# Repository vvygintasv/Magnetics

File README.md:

# Magnetics
Repository for reading Mag3100 sensord with stm controllers

Hello!
Your task is to read MAG3100 magnetic field and acceleration readings using stm32 controllers.( prefably stm32 nucleo series)

Rules:
Your code must be easy to read, well commented and easily integratable.

Code usafe must have examples.
Program must have user guide.

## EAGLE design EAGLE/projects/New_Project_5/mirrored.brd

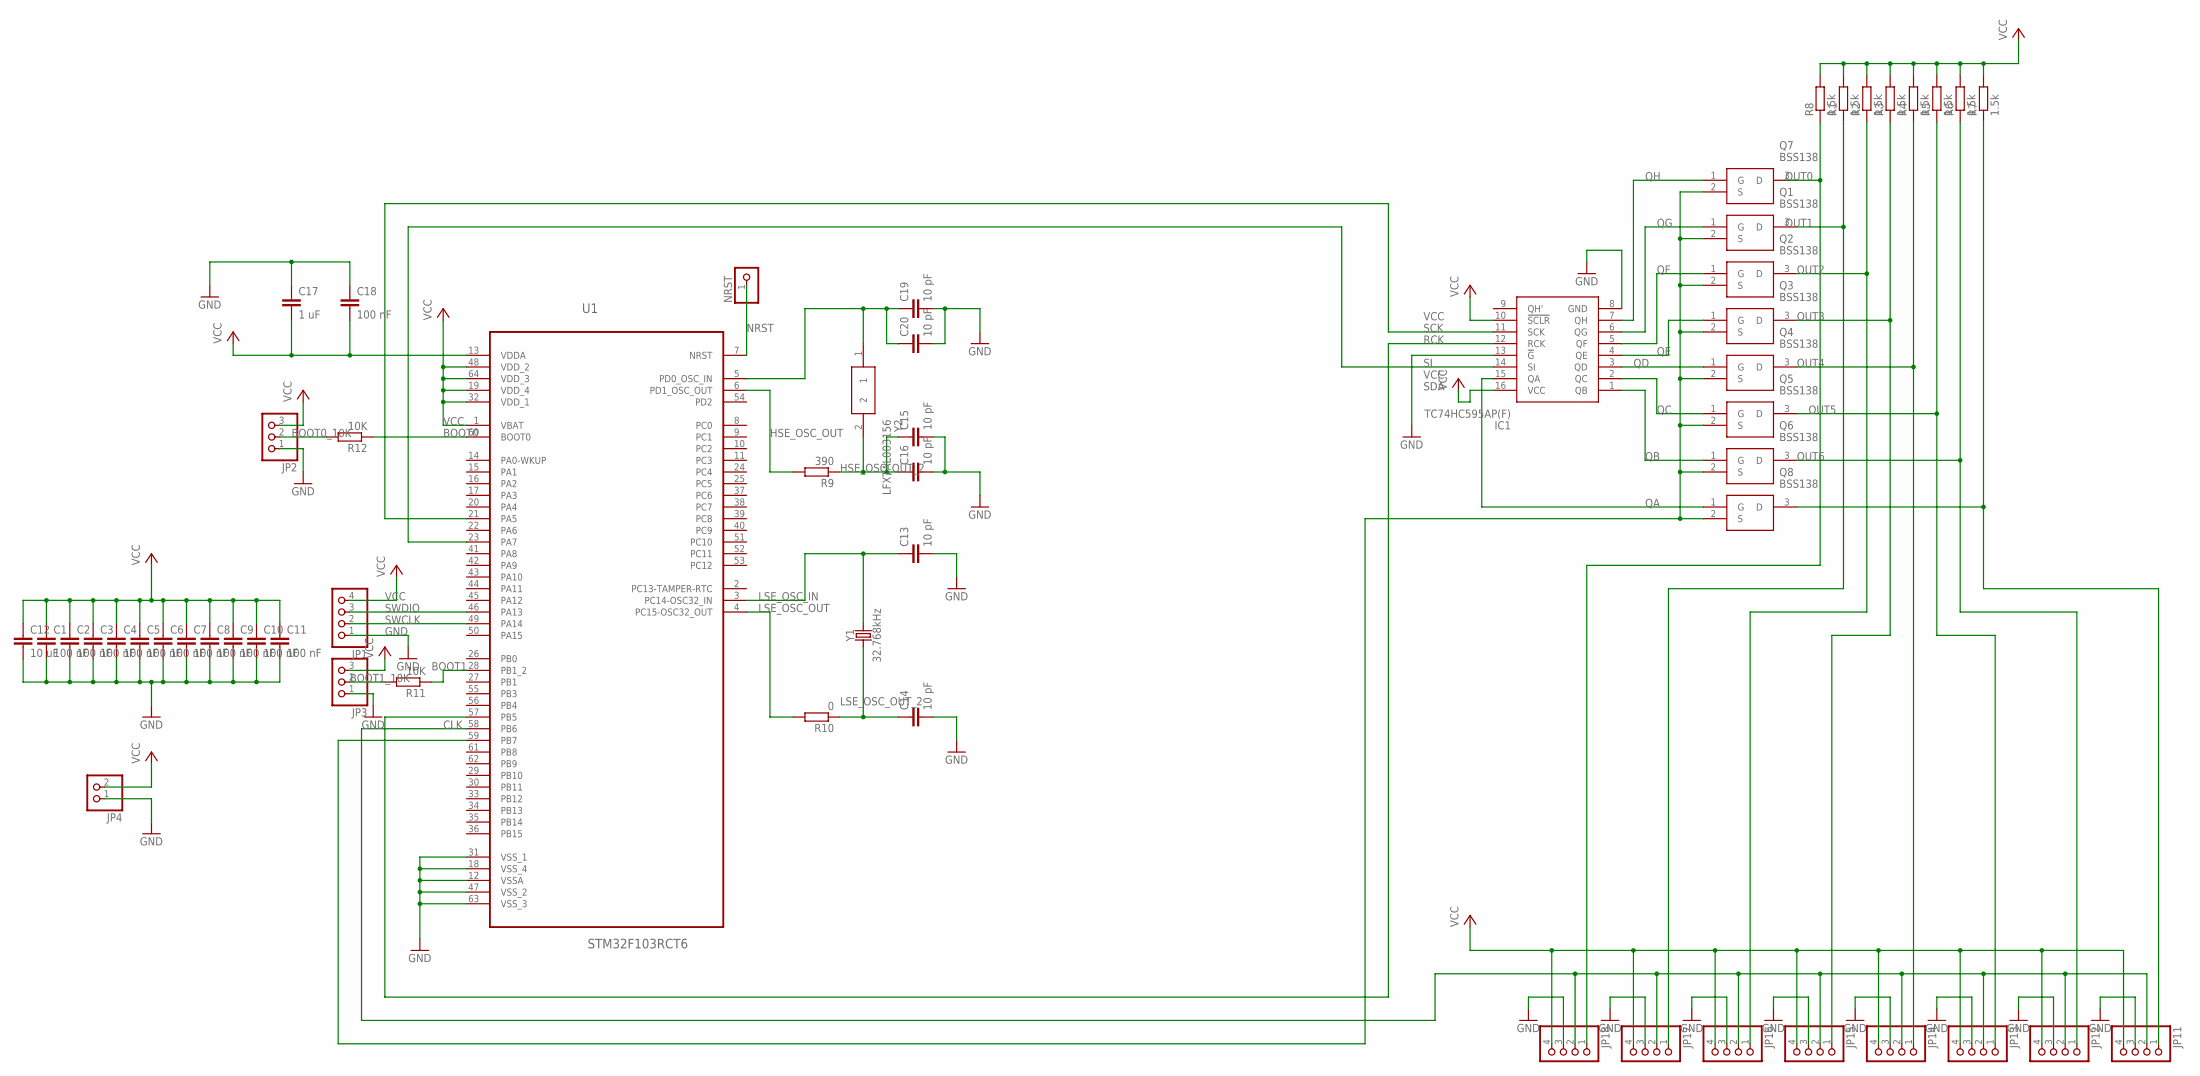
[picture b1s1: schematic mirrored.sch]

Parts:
C1, C2, C3, C4, C5, C6, C7, C8, C9, C10, C11, C18: 100 nF; C0603
C12: 10 uF; C0603
C13, C14, C15, C16, C19, C20: 10 pF; C0805
C17: 1 uF; C0603
IC1: TC74HC595AP(F); DIP762W60P254L1925H445Q16N
JP1, JP11, JP12, JP13, JP14, JP15, JP16, JP17, JP18: PINHD-1X4; 1X04
JP2, JP3: PINHD-1X3; 1X03
JP4: PINHD-1X2; 1X02
NRST: PINHD-1X1; 1X01
Q1, Q2, Q3, Q4, Q5, Q6, Q7, Q8: BSS138; SOT95P240X120-3N
R1, R2, R3, R4, R5, R6, R7, R8: 1.5k; 0207/15
R9: 390; 0207/15
R10: 0; 0207/15
R11, R12: 10K; 0207/15
U1: STM32F103RCT6; QFP50P1200X1200X160-64N
Y1: 32.768kHz; CRYSTAL-PTH-2X6-CYL
Y2: LFXTAL003156; IQD-HC-49-4H

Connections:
BOOT0: R12.1, U1.60 (BOOT0)
BOOT0_10K: JP2.2, R12.2
BOOT1: R11.1, U1.28 (PB1_2)
BOOT1_10K: JP3.2, R11.2
CLK: JP11.2, JP12.2, JP13.2, JP14.2, JP15.2, JP16.2, JP17.2, JP18.2, U1.58 (PB6)
GND: C1.2, C2.2, C3.2, C4.2, C5.2, C6.2, C7.2, C8.2, C9.2, C10.2, C11.2, C12.2, C13.2, C14.2, C15.2, C16.2, C17.1, C18.1, C19.2, C20.2, IC1.8 (GND), IC1.13 (!G), JP1.1, JP2.1, JP3.1, JP4.1, JP11.3, JP12.3, JP13.3, JP14.3, JP15.3, JP16.3, JP17.3, JP18.3, U1.12 (VSSA), U1.18 (VSS_4), U1.31 (VSS_1), U1.47 (VSS_2), U1.63 (VSS_3)
HSE_OSC_IN: C19.1, C20.1, U1.5 (PD0_OSC_IN), Y2.1
HSE_OSC_OUT: R9.2, U1.6 (PD1_OSC_OUT)
HSE_OSC_OUT_2: C15.1, C16.1, R9.1, Y2.2
LSE_OSC_IN: C13.1, U1.3 (PC14-OSC32_IN), Y1.2
LSE_OSC_OUT: R10.2, U1.4 (PC15-OSC32_OUT)
LSE_OSC_OUT_2: C14.1, R10.1, Y1.1
NRST: NRST.1, U1.7 (NRST)
OUT0: JP18.1, Q7.3 (D), R8.1
OUT1: JP17.1, Q1.3 (D), R1.1
OUT2: JP16.1, Q2.3 (D), R2.1
OUT3: JP15.1, Q3.3 (D), R3.1
OUT4: JP14.1, Q4.3 (D), R4.1
OUT5: JP13.1, Q5.3 (D), R5.1
OUT6: JP12.1, Q6.3 (D), R6.1
OUT7: JP11.1, Q8.3 (D), R7.1
QA: IC1.15 (QA), Q8.1 (G)
QB: IC1.1 (QB), Q6.1 (G)
QC: IC1.2 (QC), Q5.1 (G)
QD: IC1.3 (QD), Q4.1 (G)
QE: IC1.4 (QE), Q3.1 (G)
QF: IC1.5 (QF), Q2.1 (G)
QG: IC1.6 (QG), Q1.1 (G)
QH: IC1.7 (QH), Q7.1 (G)
RCK: IC1.12 (RCK), U1.57 (PB5)
SCK: IC1.11 (SCK), U1.21 (PA5)
SDA: Q1.2 (S), Q2.2 (S), Q3.2 (S), Q4.2 (S), Q5.2 (S), Q6.2 (S), Q7.2 (S), Q8.2 (S), U1.59 (PB7)
SI: IC1.14 (SI), U1.23 (PA7)
SWCLK: JP1.2, U1.49 (PA14)
SWDIO: JP1.3, U1.46 (PA13)
VCC: C1.1, C2.1, C3.1, C4.1, C5.1, C6.1, C7.1, C8.1, C9.1, C10.1, C11.1, C12.1, C17.2, C18.2, IC1.10 (!SCLR), IC1.16 (VCC), JP1.4, JP2.3, JP3.3, JP4.2, JP11.4, JP12.4, JP13.4, JP14.4, JP15.4, JP16.4, JP17.4, JP18.4, R1.2, R2.2, R3.2, R4.2, R5.2, R6.2, R7.2, R8.2, U1.1 (VBAT), U1.13 (VDDA), U1.19 (VDD_4), U1.32 (VDD_1), U1.48 (VDD_2), U1.64 (VDD_3)

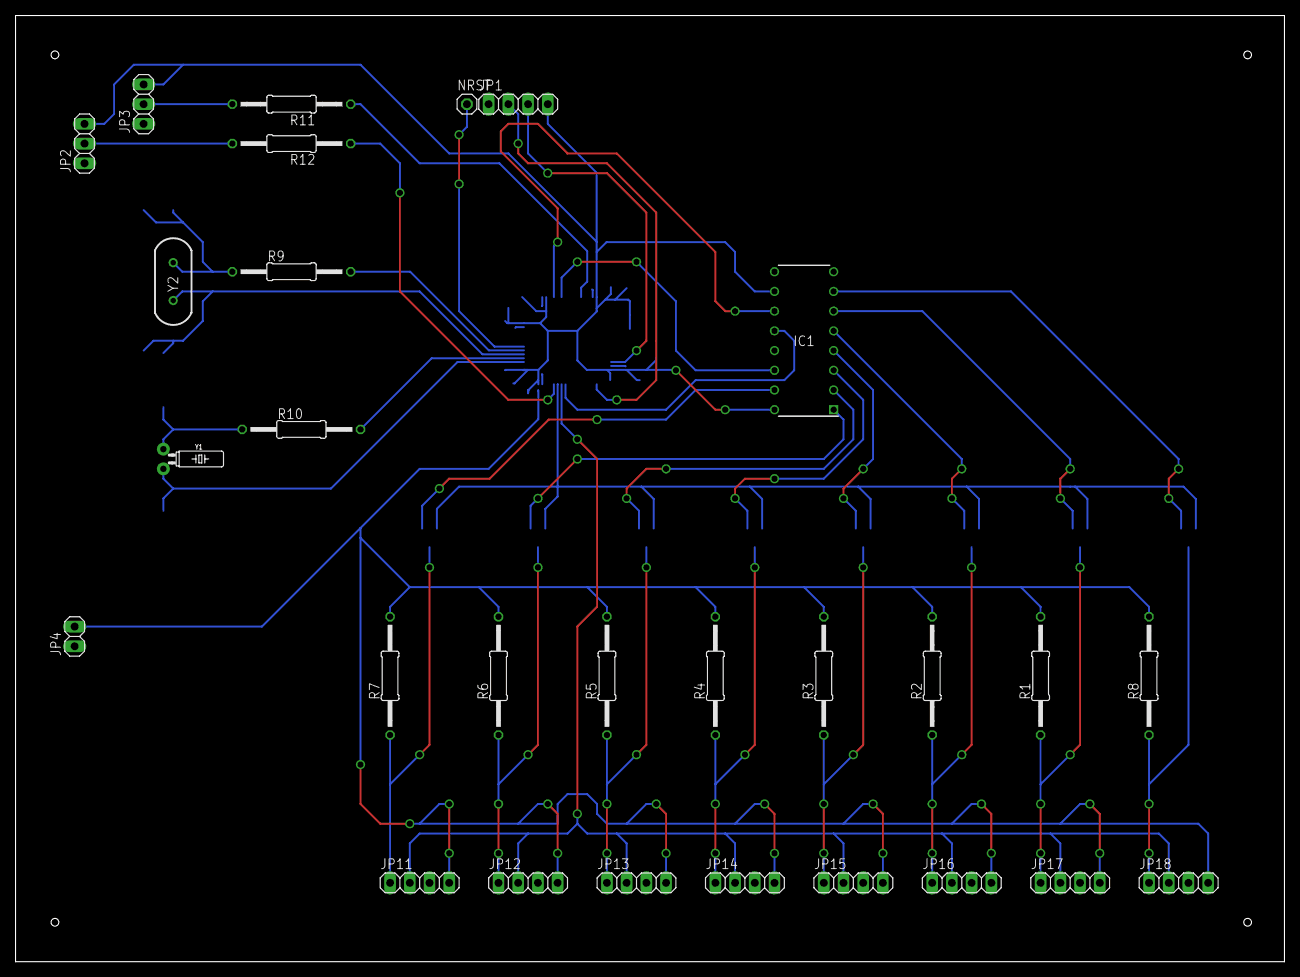
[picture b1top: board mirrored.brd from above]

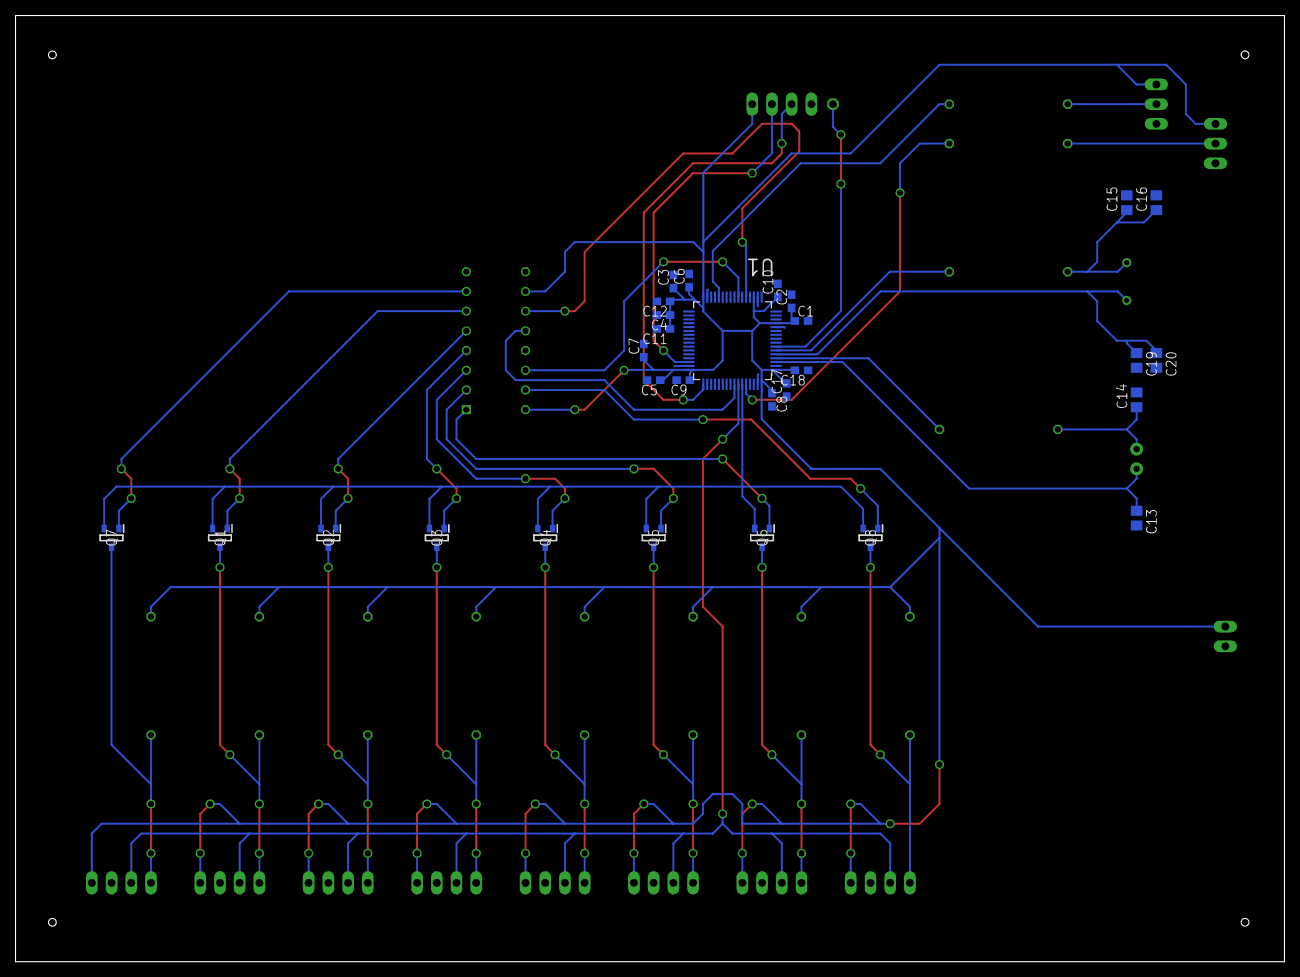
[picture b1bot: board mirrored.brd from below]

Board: 2 copper layers, 163.5 x 121.9 mm, 57 parts (29 on the bottom side), 36 nets.

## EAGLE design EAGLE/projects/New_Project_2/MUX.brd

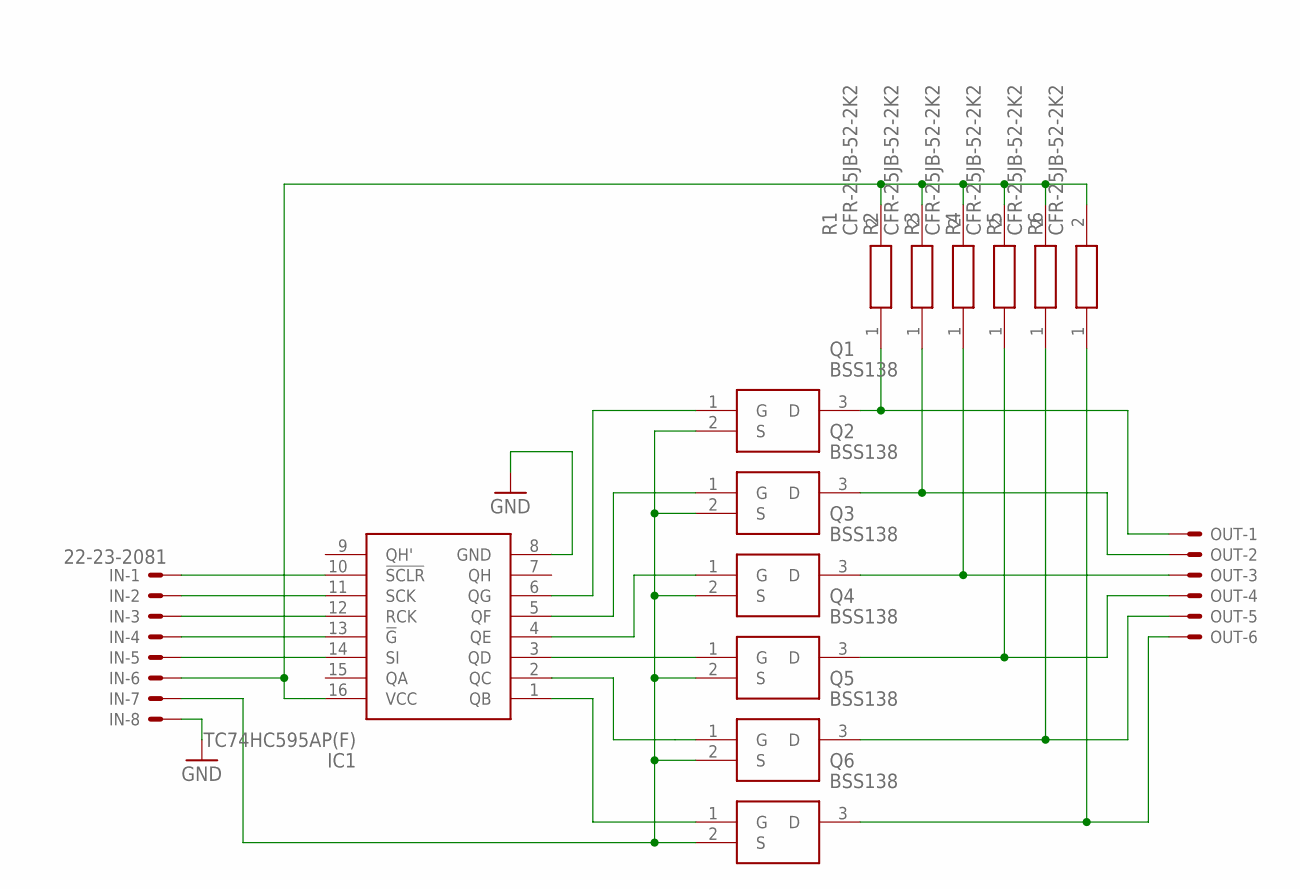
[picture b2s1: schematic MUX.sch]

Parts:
IC1: TC74HC595AP(F); DIP762W60P254L1925H445Q16N
IN: 22-23-2081
OUT: 22-23-2061
Q1, Q2, Q3, Q4, Q5, Q6: BSS138; SOT95P240X120-3N
R1, R2, R3, R4, R5, R6: CFR-25JB-52-2K2; RESAD1590W60L630D240

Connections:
GND: IC1.8 (GND), IN.8
unnamed: IN.7, Q1.2 (S), Q2.2 (S), Q3.2 (S), Q4.2 (S), Q5.2 (S), Q6.2 (S)
unnamed: IC1.1 (QB), Q6.1 (G)
unnamed: IC1.3 (QD), Q4.1 (G)
unnamed: IC1.2 (QC), Q5.1 (G)
unnamed: IC1.6 (QG), Q1.1 (G)
unnamed: IC1.5 (QF), Q2.1 (G)
unnamed: IC1.4 (QE), Q3.1 (G)
unnamed: IC1.10 (!SCLR), IN.1
unnamed: IC1.11 (SCK), IN.2
unnamed: IC1.12 (RCK), IN.3
unnamed: IC1.13 (!G), IN.4
unnamed: IC1.14 (SI), IN.5
unnamed: IC1.16 (VCC), IN.6, R1.2, R2.2, R3.2, R4.2, R5.2, R6.2
unnamed: OUT.1, Q1.3 (D), R1.1
unnamed: OUT.2, Q2.3 (D), R2.1
unnamed: OUT.3, Q3.3 (D), R3.1
unnamed: OUT.4, Q4.3 (D), R4.1
unnamed: OUT.5, Q5.3 (D), R5.1
unnamed: OUT.6, Q6.3 (D), R6.1

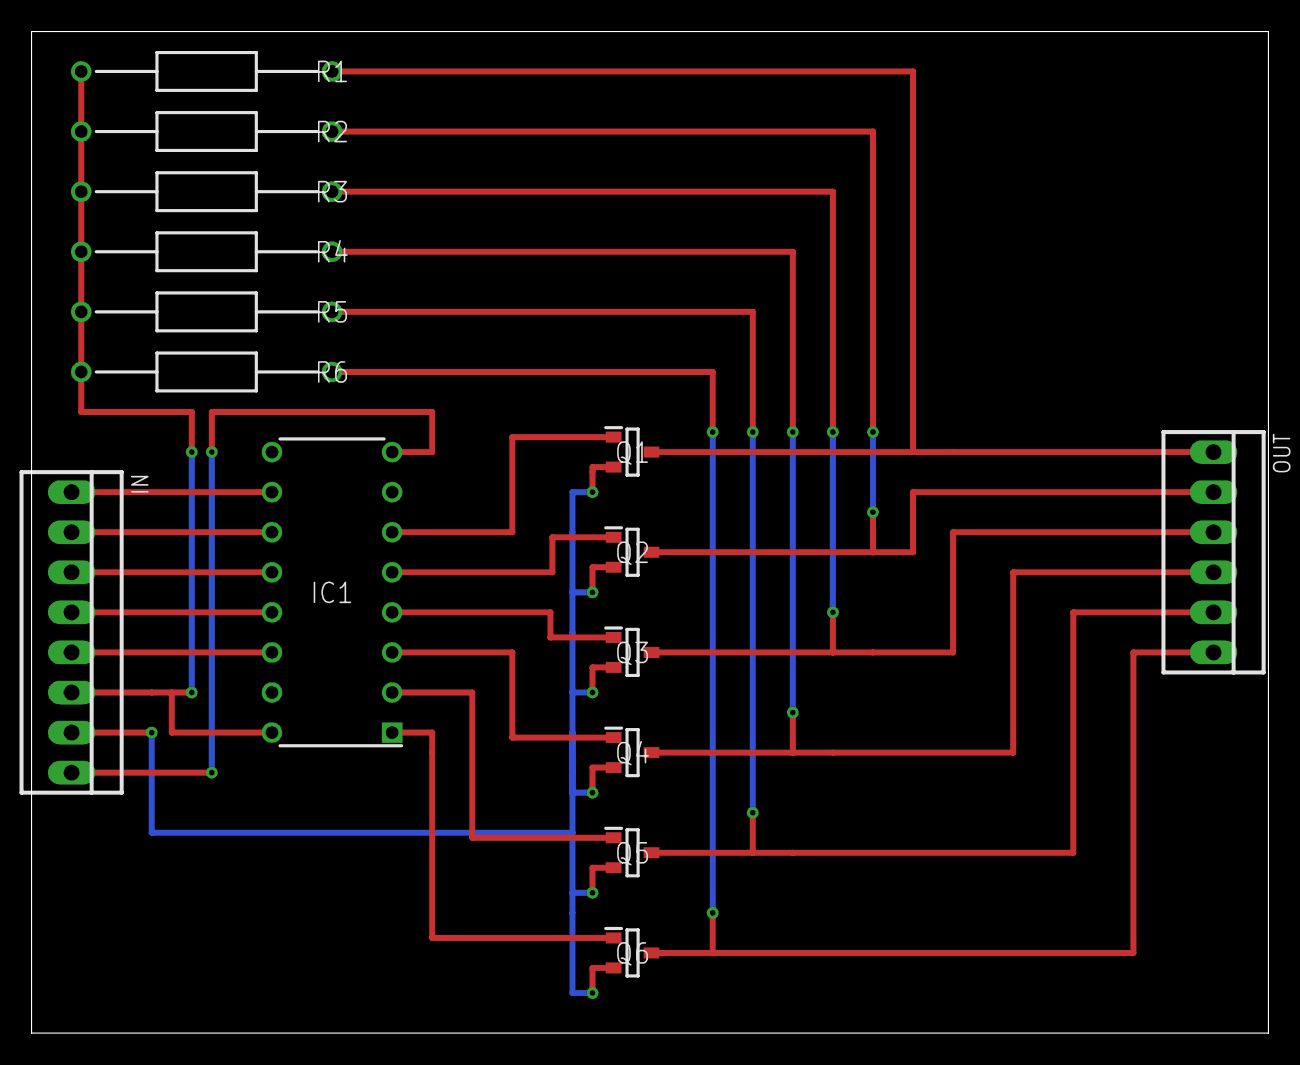
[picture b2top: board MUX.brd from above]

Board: 2 copper layers, 78.4 x 63.5 mm, 15 parts (0 on the bottom side), 20 nets.

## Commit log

2019-01-21 Added datasheet of MAG3110
2019-01-22 Surinkta info / Simulink pradzia
2019-01-23 Added file with differential equations
2019-01-23 Added Arduino Mag files
2019-01-23 Renamed files
2019-01-23 Update Finding magnet differential equations.nb
    Deleted lines for testing with known values, those can be found in the other file
2019-01-23 Algoritmas perkeltas i arduino koda
2019-01-24 Working Arduino Code for Magnetometer
2019-01-24 Moved Around Files
2019-01-25 STM Code, moved files
2019-01-25 Title
2019-01-25 Added Report
2019-01-28 Attempting to fix bug / added report
2019-01-29 Attempts to Debug
2019-01-29 Report
2019-01-30 Arduino code and report
2019-01-31 Update Mag3110Soft.ino
    Changed functions to work with one sensor at a time
2019-01-31 Fixing bugs
2019-01-31 Testing fixes
2019-02-01 Delete Report_01_31.docx
    Report didnt save, will rewrite later
2019-02-01 attempted bugfixing
2019-02-05 Bugfixing attempts
    Unsuccesful
2019-02-05 Reading functions changed
2019-02-05 More bugfixing attempts
    Unsuccessful
2019-02-06 Load Cell work reports
2019-02-07 HX711 code from 02-06
2019-02-07 STM bug fixed
2019-02-08 Laboratorinio ataskaita
2019-02-08 Added wire colors
2019-02-11 Added Reports
    Also added magnetometer printing to console.
2019-02-11 Printf attempts
2019-02-12 Added comments to code
2019-02-12 couple more comments
2019-02-12 typo
2019-02-13 New functions in magnetmath.c
    Creating grid of expected magnetic field values, sensor value comparison to grid.
    Have not been tested
    Comments will be added later
2019-02-13 Changed arrays to 1D
2019-02-13 Create TestingMagnetFieldEquations.ino
    Attempting the same equations in arduino IDE for debugging purposes
2019-02-13 Reports added
2019-02-14 Added functions for table
    Made functions to recalculate expected magnetic field every time it is checked. Result is slow but doesnt use memory.
    It has been commented and table creation rewritten. Getting ready for a dictionary lookup.
2019-02-14 Small edits, typo fixes
2019-02-18 Information about the two chips
2019-02-20 Update main.c
    Made clear where to enter height from ground of magnetometer
2019-02-20 Create ir_analog_sensor.ino
    For testing an IR light and sensor
2019-02-21 datasheets of multiplexing solutions
2019-02-26 Monday and tuesday work
    Designed custom MUX PCB on EAGLE. Used CubeMX to generate skeleton code for additional pins to control Shift Register chip.
2019-02-27 Rewrote code to generalize sensor number and use a shift register
2019-02-27 Started writing PID based line following
2019-02-27 Added missing reports
2019-02-28 Added reset of signal pin before selecting sensor
2019-02-28 Update main.c
    Added setting of NSCLR pin at program startup
2019-02-28 Update Magnet.c
    Added clear of register data before sensor selection
2019-03-04 Added comments
2019-03-04 Update Magnet.c
    Added more comments
2019-03-08 Changes
    Rewritten code with HAL SPI commands, same problem remains.
    Added report for the week.
2019-03-12 Debugging
2019-03-20 Working testing code
2019-03-20 Printing correct information
2019-03-22 Update
    Made sensor selection compatible with additional shift register chips
2019-03-22 Update
    Deleted experimental code which was commented out
    Added seperate function to send a desired buffer to the shift register serial input
2019-03-22 Update
    Deleted more commented code
2019-03-22 Update
    Commented out unnecessary lines of code, but which may be useful in the future
2019-04-08 Eagle projects

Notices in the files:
parts and their libraries:
SparkFun-Clocks: Licensing: Creative Commons ShareAlike 4.0 International - https://creativecommons.org/licenses/by-sa/4.0
